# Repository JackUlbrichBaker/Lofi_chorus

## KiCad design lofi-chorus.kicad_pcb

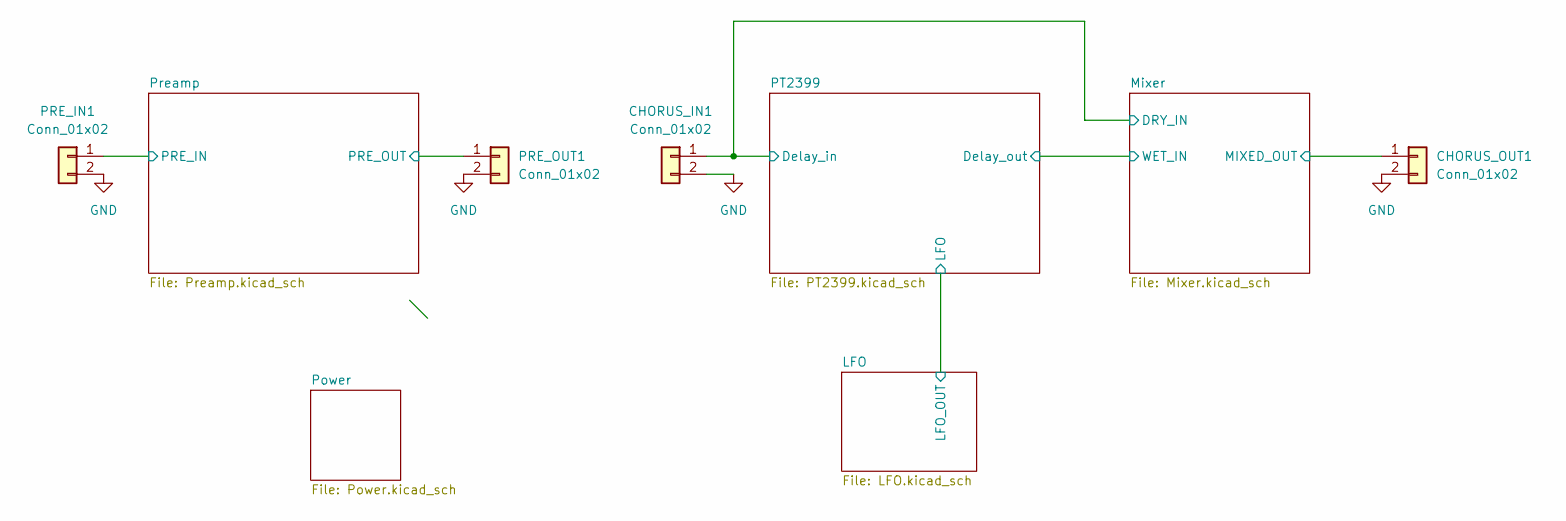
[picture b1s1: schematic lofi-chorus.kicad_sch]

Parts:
CHORUS_IN1: Conn_01x02; PinHeader_1x02_P2.54mm_Vertical
CHORUS_OUT1: Conn_01x02; PinHeader_1x02_P2.54mm_Vertical
PRE_IN1: Conn_01x02; PinHeader_1x02_P2.54mm_Vertical
PRE_OUT1: Conn_01x02; PinHeader_1x02_P2.54mm_Vertical

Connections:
/Mixer/DRY_IN: CHORUS_IN1.1; also elsewhere on the board
/Mixer/MIXED_OUT: CHORUS_OUT1.1; also elsewhere on the board
/Preamp/PRE_IN: PRE_IN1.1; also elsewhere on the board
/Preamp/PRE_OUT: PRE_OUT1.1; also elsewhere on the board
GND: CHORUS_IN1.2, CHORUS_OUT1.2, PRE_IN1.2, PRE_OUT1.2; also elsewhere on the board

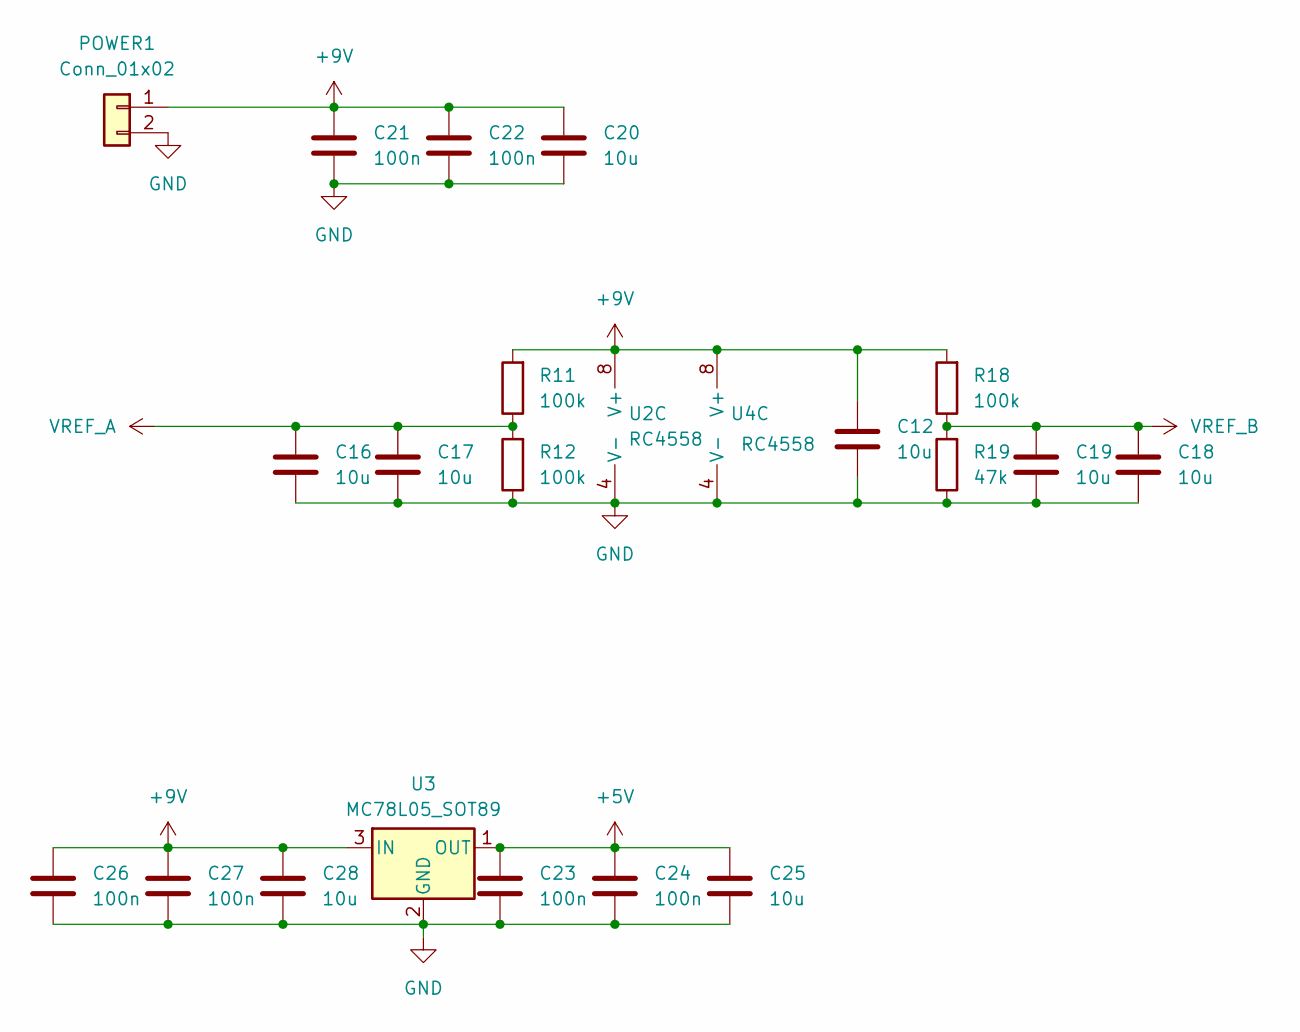
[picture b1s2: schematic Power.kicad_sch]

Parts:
C12, C16, C17, C18, C19, C20, C25, C28: 10u; C_0805_2012Metric
C21, C22, C23, C24, C26, C27: 100n; C_0805_2012Metric
POWER1: Conn_01x02; PinHeader_1x02_P2.54mm_Vertical
R11, R12, R18: 100k; R_0805_2012Metric
R19: 47k; R_0805_2012Metric
U2, U4: RC4558; SOIC-8W_5.3x5.3mm_P1.27mm
U3: MC78L05_SOT89; SOIC-8_3.9x4.9mm_P1.27mm

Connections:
+5V: C23.2, C24.2, C25.2, U3.1 (OUT); also elsewhere on the board
+9V: C12.2, C20.2, C21.2, C22.2, C26.2, C27.2, C28.2, POWER1.1, R11.2, R18.2, U2.8 (V+), U3.3 (IN), U4.8 (V+)
GND: C12.1, C16.1, C17.1, C18.1, C19.1, C20.1, C21.1, C22.1, C23.1, C24.1, C25.1, C26.1, C27.1, C28.1, POWER1.2, R12.1, R19.1, U2.4 (V-), U3.2 (GND), U4.4 (V-); also elsewhere on the board
VREF_A: C16.2, C17.2, R11.1, R12.2; also elsewhere on the board
VREF_B: C18.2, C19.2, R18.1, R19.2; also elsewhere on the board

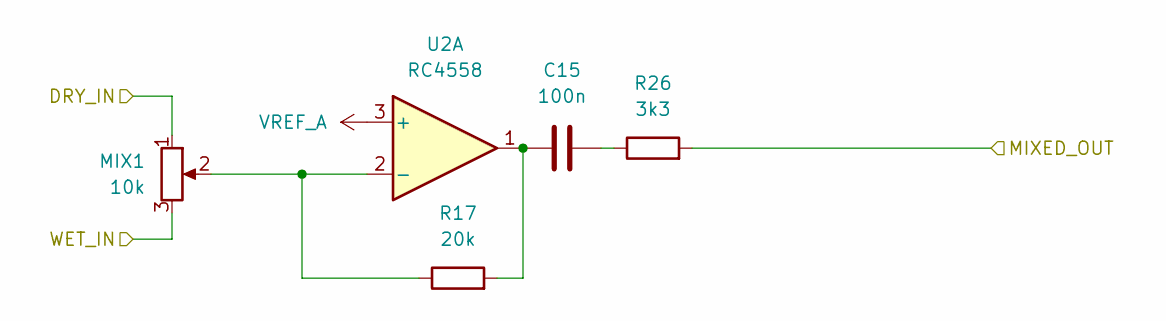
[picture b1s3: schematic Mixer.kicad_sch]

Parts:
C15: 100n; C_0805_2012Metric
MIX1: 10k; Potentiometer_Alpha_RD902F-40-00D_Dual_Vertical
R17: 20k; R_0805_2012Metric
R26: 3k3; R_0805_2012Metric
U2: RC4558; SOIC-8W_5.3x5.3mm_P1.27mm

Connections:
/Mixer/DRY_IN: MIX1.1; also elsewhere on the board
/Mixer/MIXED_OUT: R26.2; also elsewhere on the board
/Mixer/WET_IN: MIX1.3; also elsewhere on the board
unnamed: C15.1, R17.2, U2.1
unnamed: C15.2, R26.1
unnamed: MIX1.2, R17.1, U2.2 (-)
VREF_A: U2.3 (+); also elsewhere on the board

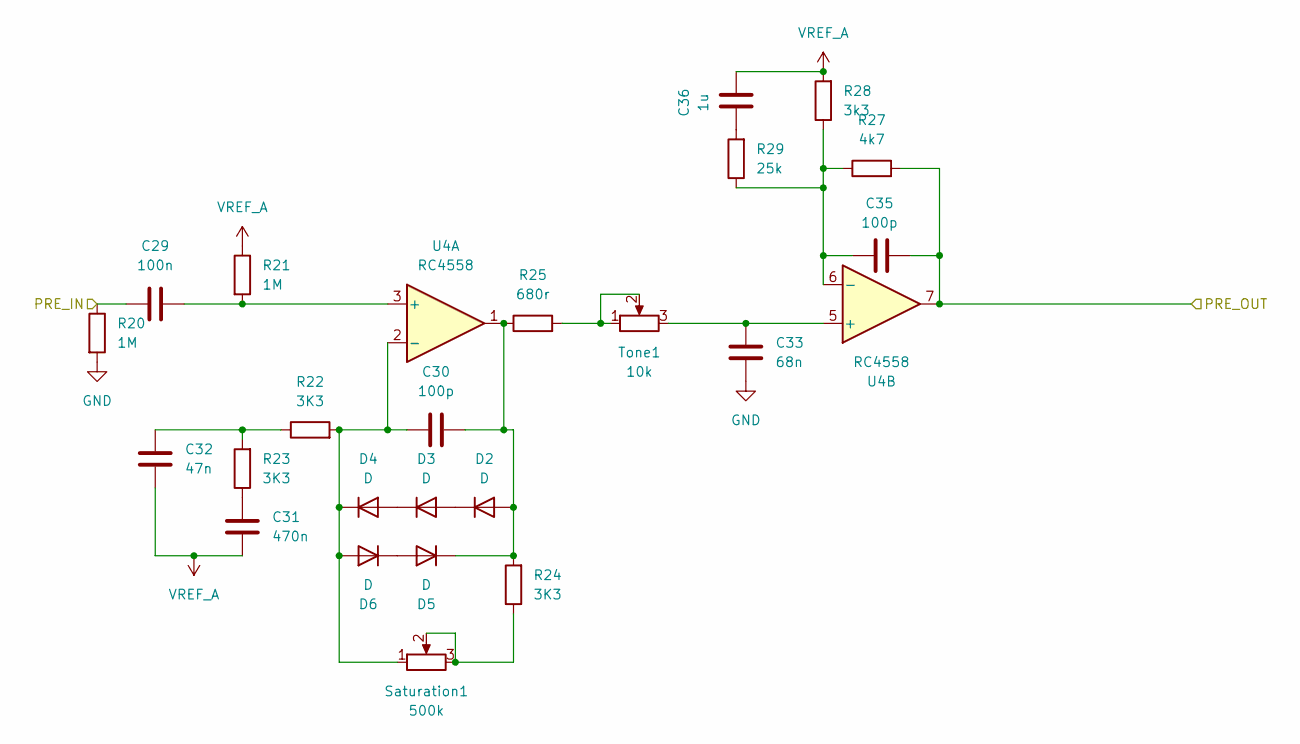
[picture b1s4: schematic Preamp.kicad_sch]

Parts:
C29: 100n; C_0805_2012Metric
C30, C35: 100p; C_0805_2012Metric
C31: 470n; C_0805_2012Metric
C32: 47n; C_0805_2012Metric
C33: 68n; C_0805_2012Metric
C36: 1u; C_0805_2012Metric
D2, D3, D4, D5, D6: D; D_0603_1608Metric
R20, R21: 1M; R_0805_2012Metric
R22, R23, R24: 3K3; R_0805_2012Metric
R25: 680r; R_0805_2012Metric
R27: 4k7; R_0805_2012Metric
R28: 3k3; R_0805_2012Metric
R29: 25k; R_0805_2012Metric
Saturation1: 500k; Potentiometer_Alpha_RD902F-40-00D_Dual_Vertical
Tone1: 10k; Potentiometer_Alpha_RD902F-40-00D_Dual_Vertical
U4: RC4558; SOIC-8W_5.3x5.3mm_P1.27mm

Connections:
/Preamp/PRE_IN: C29.1, R20.1; also elsewhere on the board
/Preamp/PRE_OUT: C35.2, R27.2, U4.7; also elsewhere on the board
GND: C33.1, R20.2; also elsewhere on the board
unnamed: C31.2, R23.1
unnamed: C32.2, R22.1, R23.2
unnamed: C36.1, R29.2
unnamed: C30.2, D2.2 (A), D5.1 (K), R24.2, R25.1, U4.1
unnamed: D2.1 (K), D3.2 (A)
unnamed: D3.1 (K), D4.2 (A)
unnamed: C30.1, D4.1 (K), D6.2 (A), R22.2, Saturation1.1, U4.2 (-)
unnamed: D5.2 (A), D6.1 (K)
unnamed: R24.1, Saturation1.2, Saturation1.3
unnamed: R25.2, Tone1.1, Tone1.2
unnamed: C29.2, R21.2, U4.3 (+)
unnamed: C33.2, Tone1.3, U4.5 (+)
unnamed: C35.1, R27.1, R28.1, R29.1, U4.6 (-)
VREF_A: C31.1, C32.1, C36.2, R21.1, R28.2; also elsewhere on the board

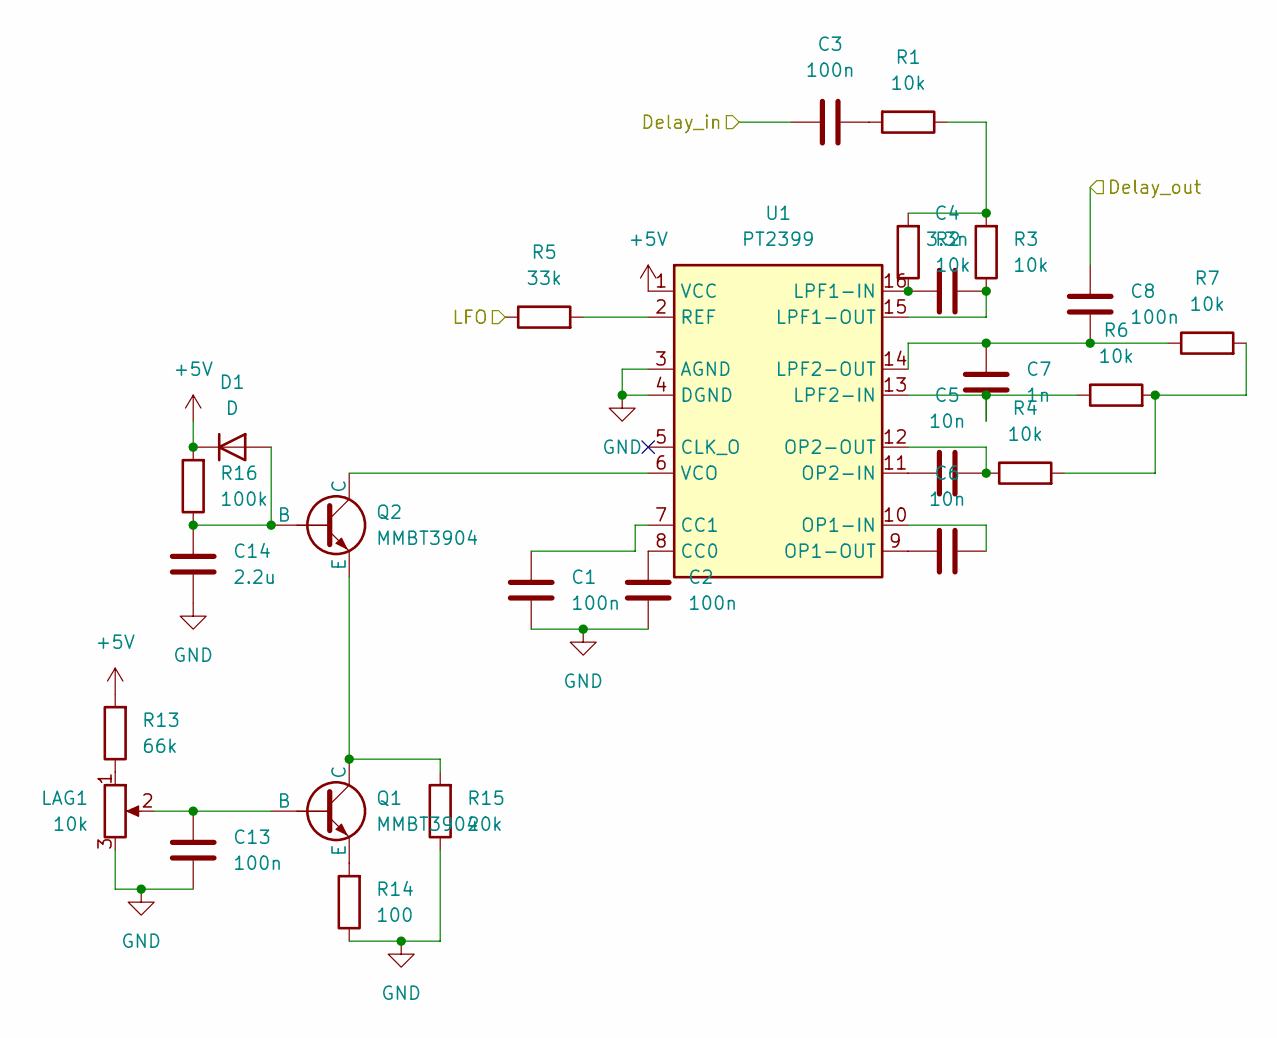
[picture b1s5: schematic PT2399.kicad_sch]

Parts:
C1, C2, C3, C8, C13: 100n; C_0805_2012Metric
C4: 3.3n; C_0805_2012Metric
C5, C6: 10n; C_0805_2012Metric
C7: 1n; C_0805_2012Metric
C14: 2.2u; C_0805_2012Metric
D1: D; D_0603_1608Metric
LAG1: 10k; Potentiometer_Alpha_RD902F-40-00D_Dual_Vertical
Q1, Q2: MMBT3904; SOT-23-3
R1, R2, R3, R4, R6, R7: 10k; R_0805_2012Metric
R5: 33k; R_0805_2012Metric
R13: 66k; R_0805_2012Metric
R14: 100; R_0805_2012Metric
R15: 20k; R_0805_2012Metric
R16: 100k; R_0805_2012Metric
U1: PT2399; DIP-16_W7.62mm_SMDSocket_SmallPads

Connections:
+5V: D1.1 (K), R13.2, R16.2, U1.1 (VCC); also elsewhere on the board
/LFO/LFO_OUT: R5.1; also elsewhere on the board
/Mixer/DRY_IN: C3.2; also elsewhere on the board
/Mixer/WET_IN: C8.1; also elsewhere on the board
GND: C1.2, C2.2, C13.2, C14.2, LAG1.3, R14.1, R15.1, U1.3 (AGND), U1.4 (DGND); also elsewhere on the board
unnamed: C3.1, R1.2
unnamed: C14.1, D1.2 (A), Q2.2 (B), R16.1
unnamed: LAG1.1, R13.1
unnamed: C13.1, LAG1.2, Q1.2 (B)
unnamed: Q1.1 (C), Q2.3 (E), R15.2
unnamed: Q1.3 (E), R14.2
unnamed: Q2.1 (C), U1.6 (VCO)
unnamed: R1.1, R2.2, R3.2
unnamed: R4.2, R6.2, R7.2
unnamed: C2.1, U1.8 (CC0)
unnamed: C1.1, U1.7 (CC1)
unnamed: C4.2, R2.1, U1.16 (LPF1-IN)
unnamed: C4.1, R3.1, U1.15 (LPF1-OUT)
unnamed: C7.1, R6.1, U1.13 (LPF2-IN)
unnamed: C7.2, C8.2, R7.1, U1.14 (LPF2-OUT)
unnamed: C6.2, U1.10 (OP1-IN)
unnamed: C6.1, U1.9 (OP1-OUT)
unnamed: C5.1, U1.11 (OP2-IN)
unnamed: C5.2, R4.1, U1.12 (OP2-OUT)
unnamed: R5.2, U1.2 (REF)

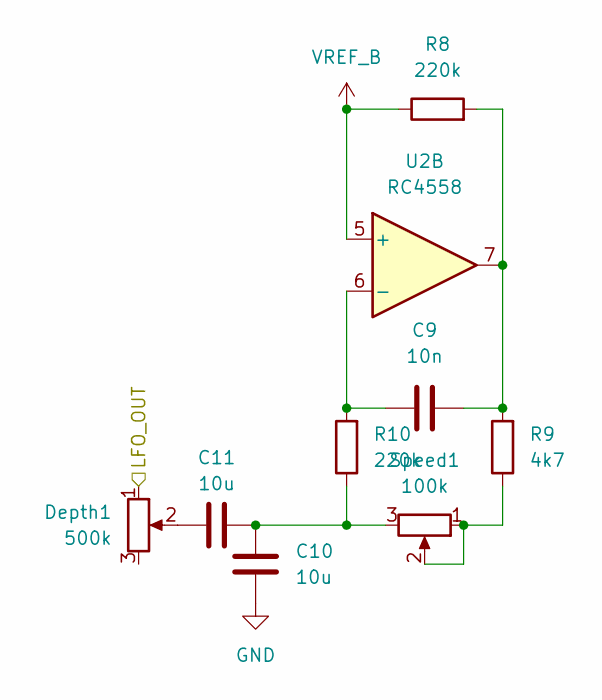
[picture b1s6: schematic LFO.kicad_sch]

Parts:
C9: 10n; C_0805_2012Metric
C10, C11: 10u; C_0805_2012Metric
Depth1: 500k; PinHeader_1x02_P2.54mm_Vertical
R8, R10: 220k; R_0805_2012Metric
R9: 4k7; R_0805_2012Metric
Speed1: 100k; Potentiometer_Alpha_RD902F-40-00D_Dual_Vertical
U2: RC4558; SOIC-8W_5.3x5.3mm_P1.27mm

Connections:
/LFO/LFO_OUT: Depth1.1; also elsewhere on the board
GND: C10.1; also elsewhere on the board
unnamed: C9.2, R8.2, R9.2, U2.7
unnamed: C10.2, C11.1, R10.1, Speed1.3
unnamed: C11.2, Depth1.2
unnamed: R9.1, Speed1.1, Speed1.2
unnamed: C9.1, R10.2, U2.6 (-)
VREF_B: R8.1, U2.5 (+); also elsewhere on the board

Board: 2 copper layers, 87 parts (0 on the bottom side), 52 nets, no tracks yet.

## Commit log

2024-12-01 init
2024-12-03 finalise schems for now
